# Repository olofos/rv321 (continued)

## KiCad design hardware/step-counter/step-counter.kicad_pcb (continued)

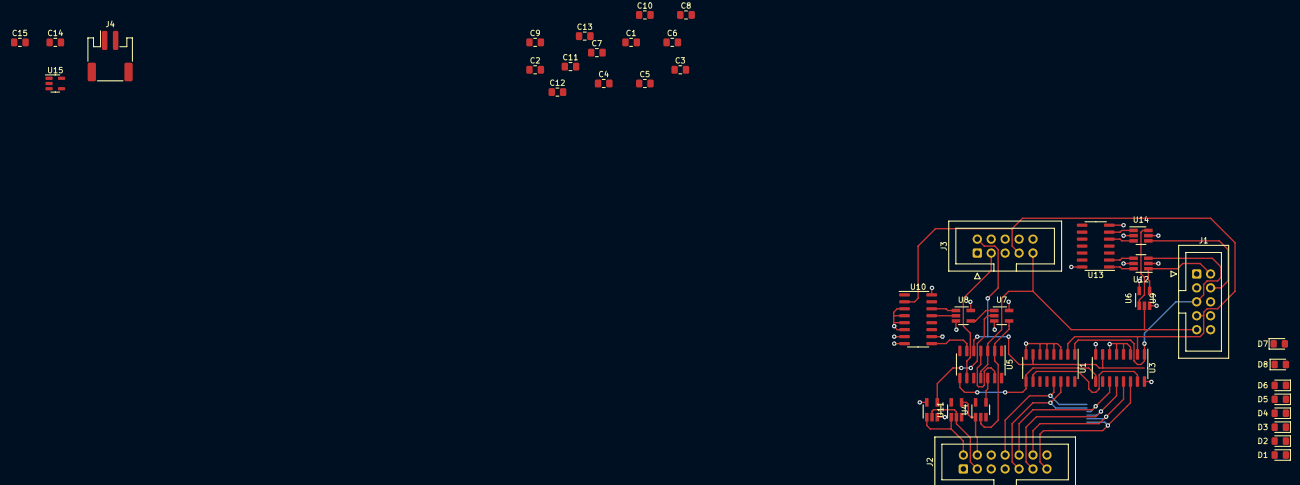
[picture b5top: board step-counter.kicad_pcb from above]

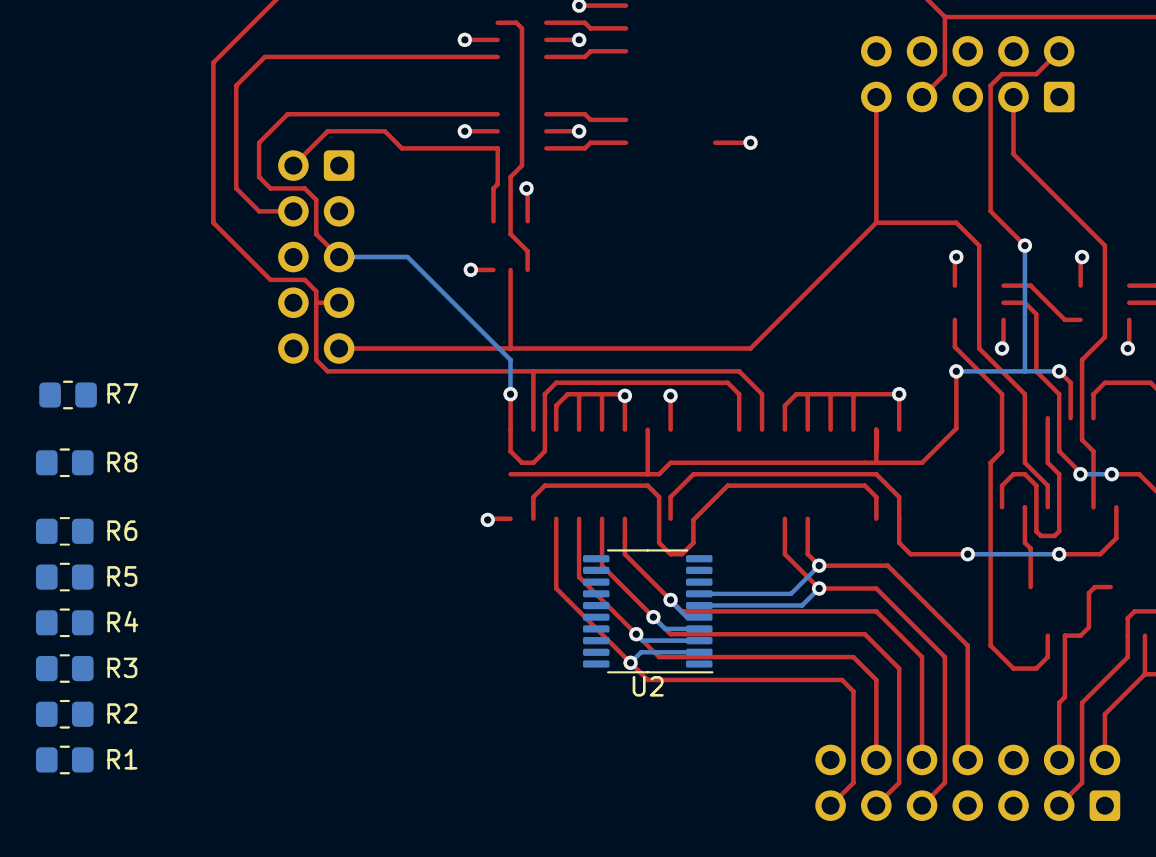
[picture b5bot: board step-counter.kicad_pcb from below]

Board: 4 copper layers, 50 parts (9 on the bottom side), 49 nets.

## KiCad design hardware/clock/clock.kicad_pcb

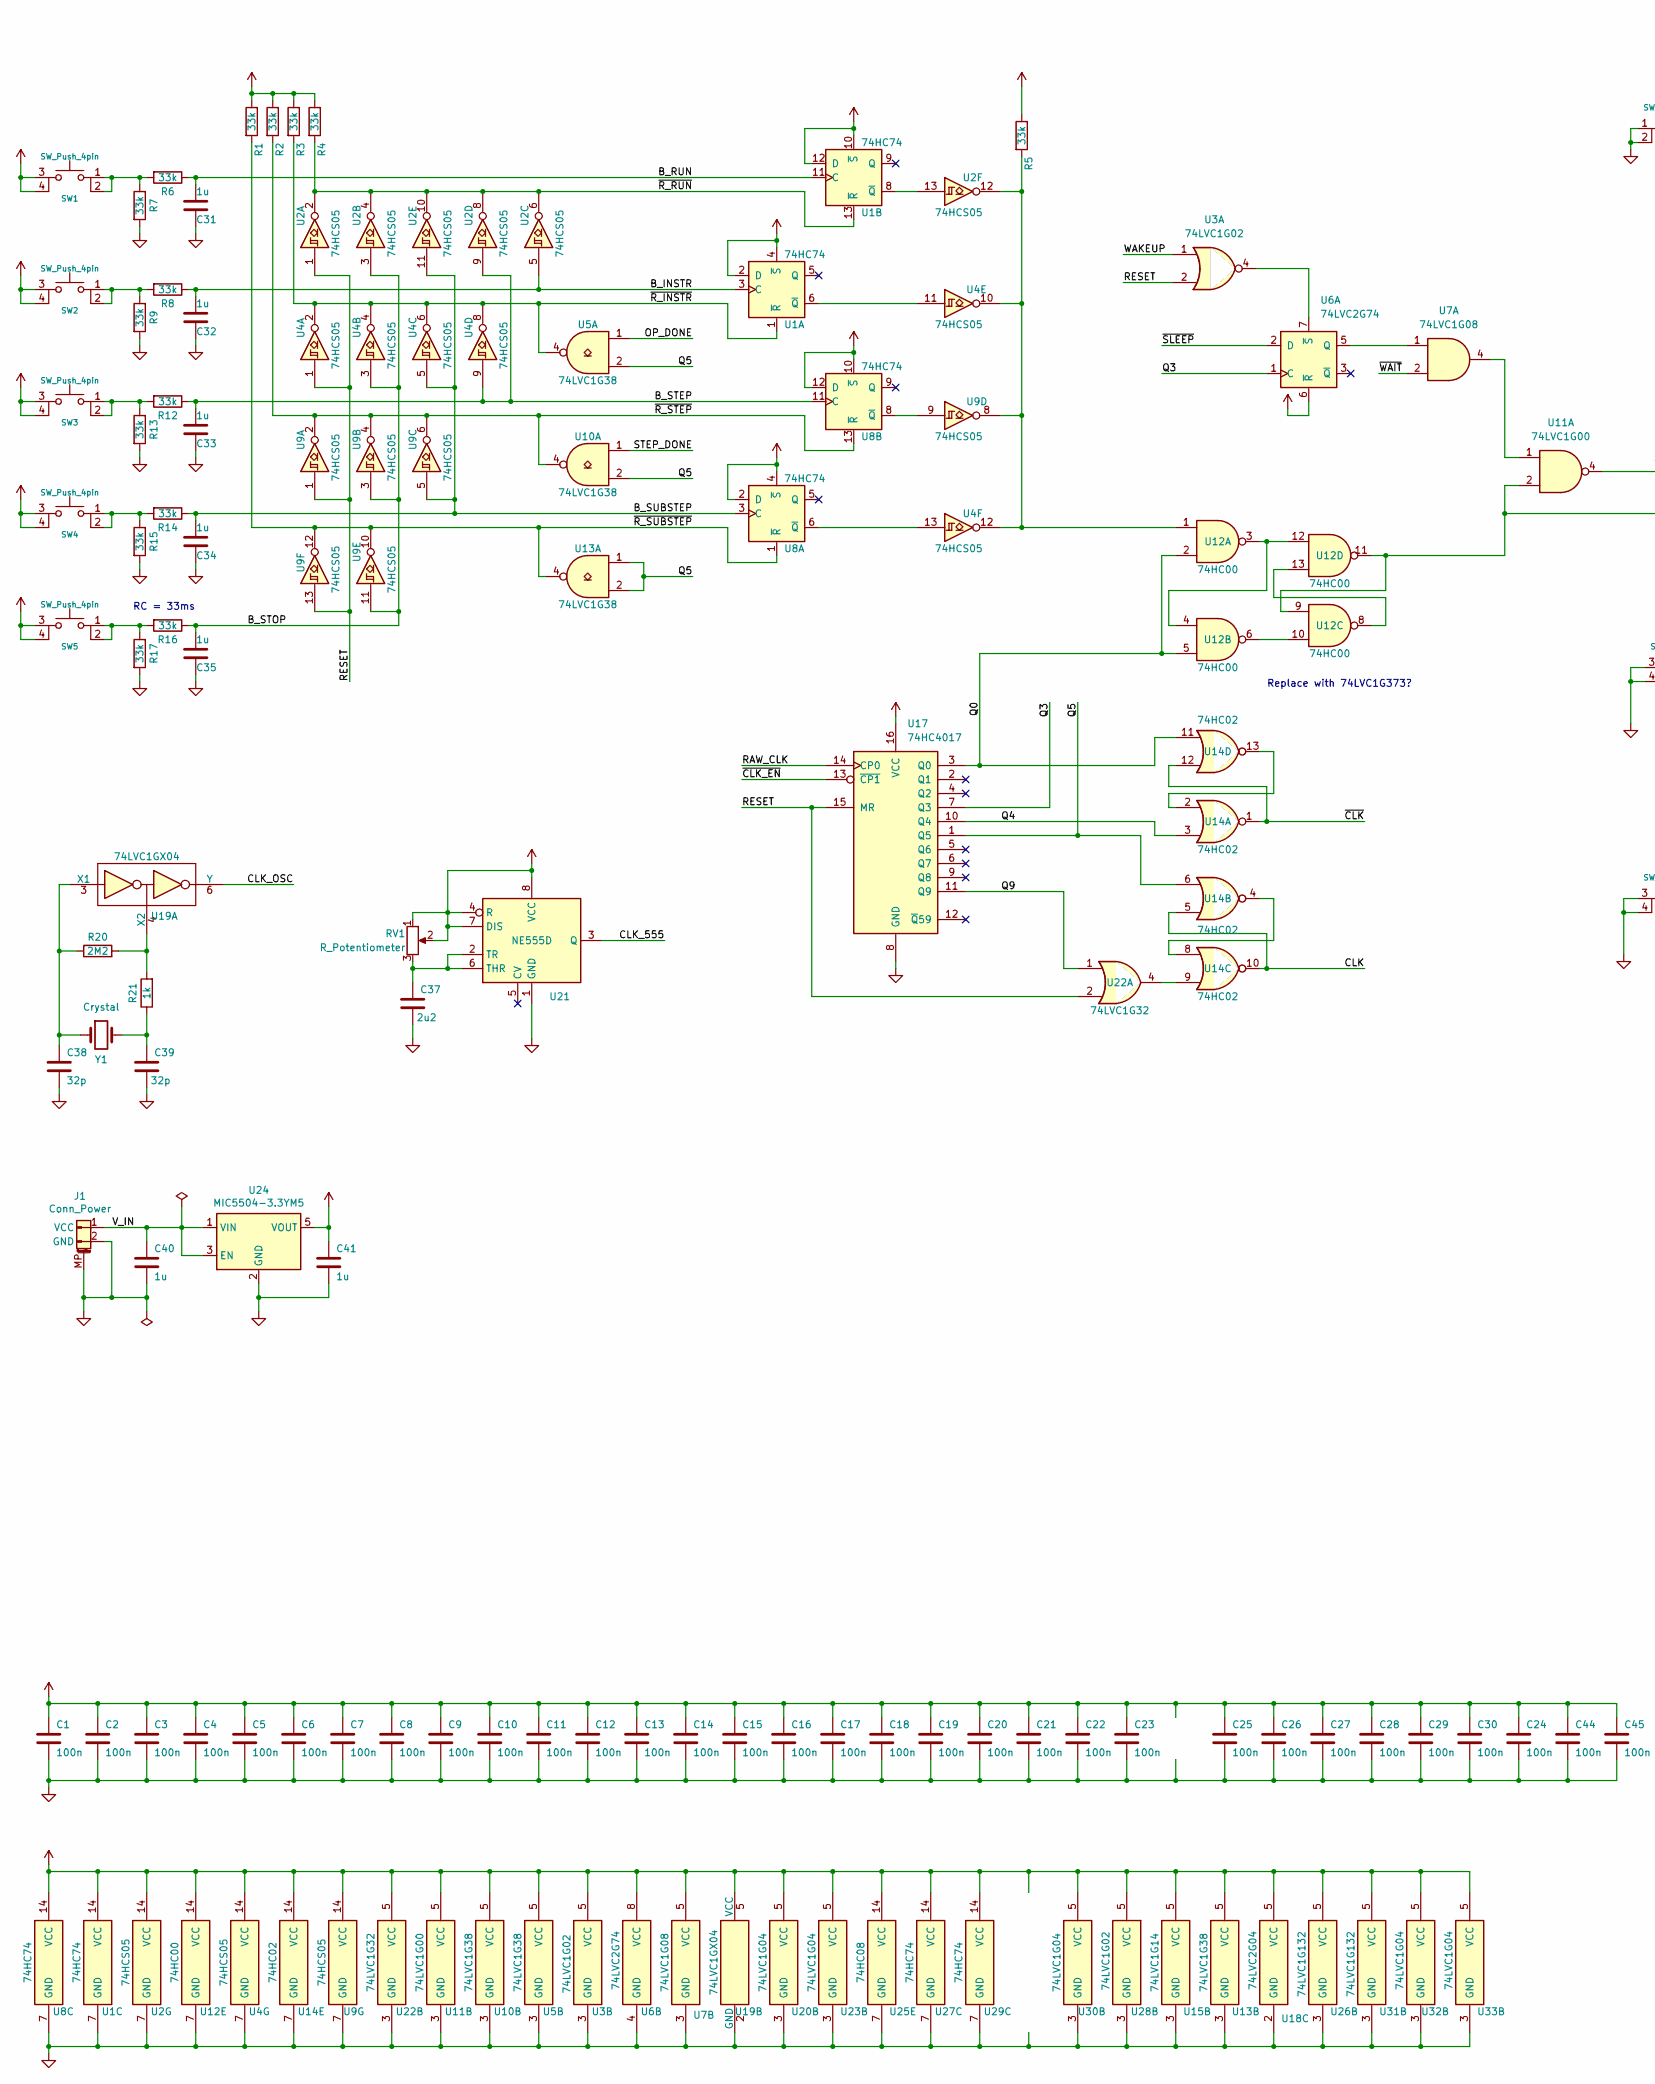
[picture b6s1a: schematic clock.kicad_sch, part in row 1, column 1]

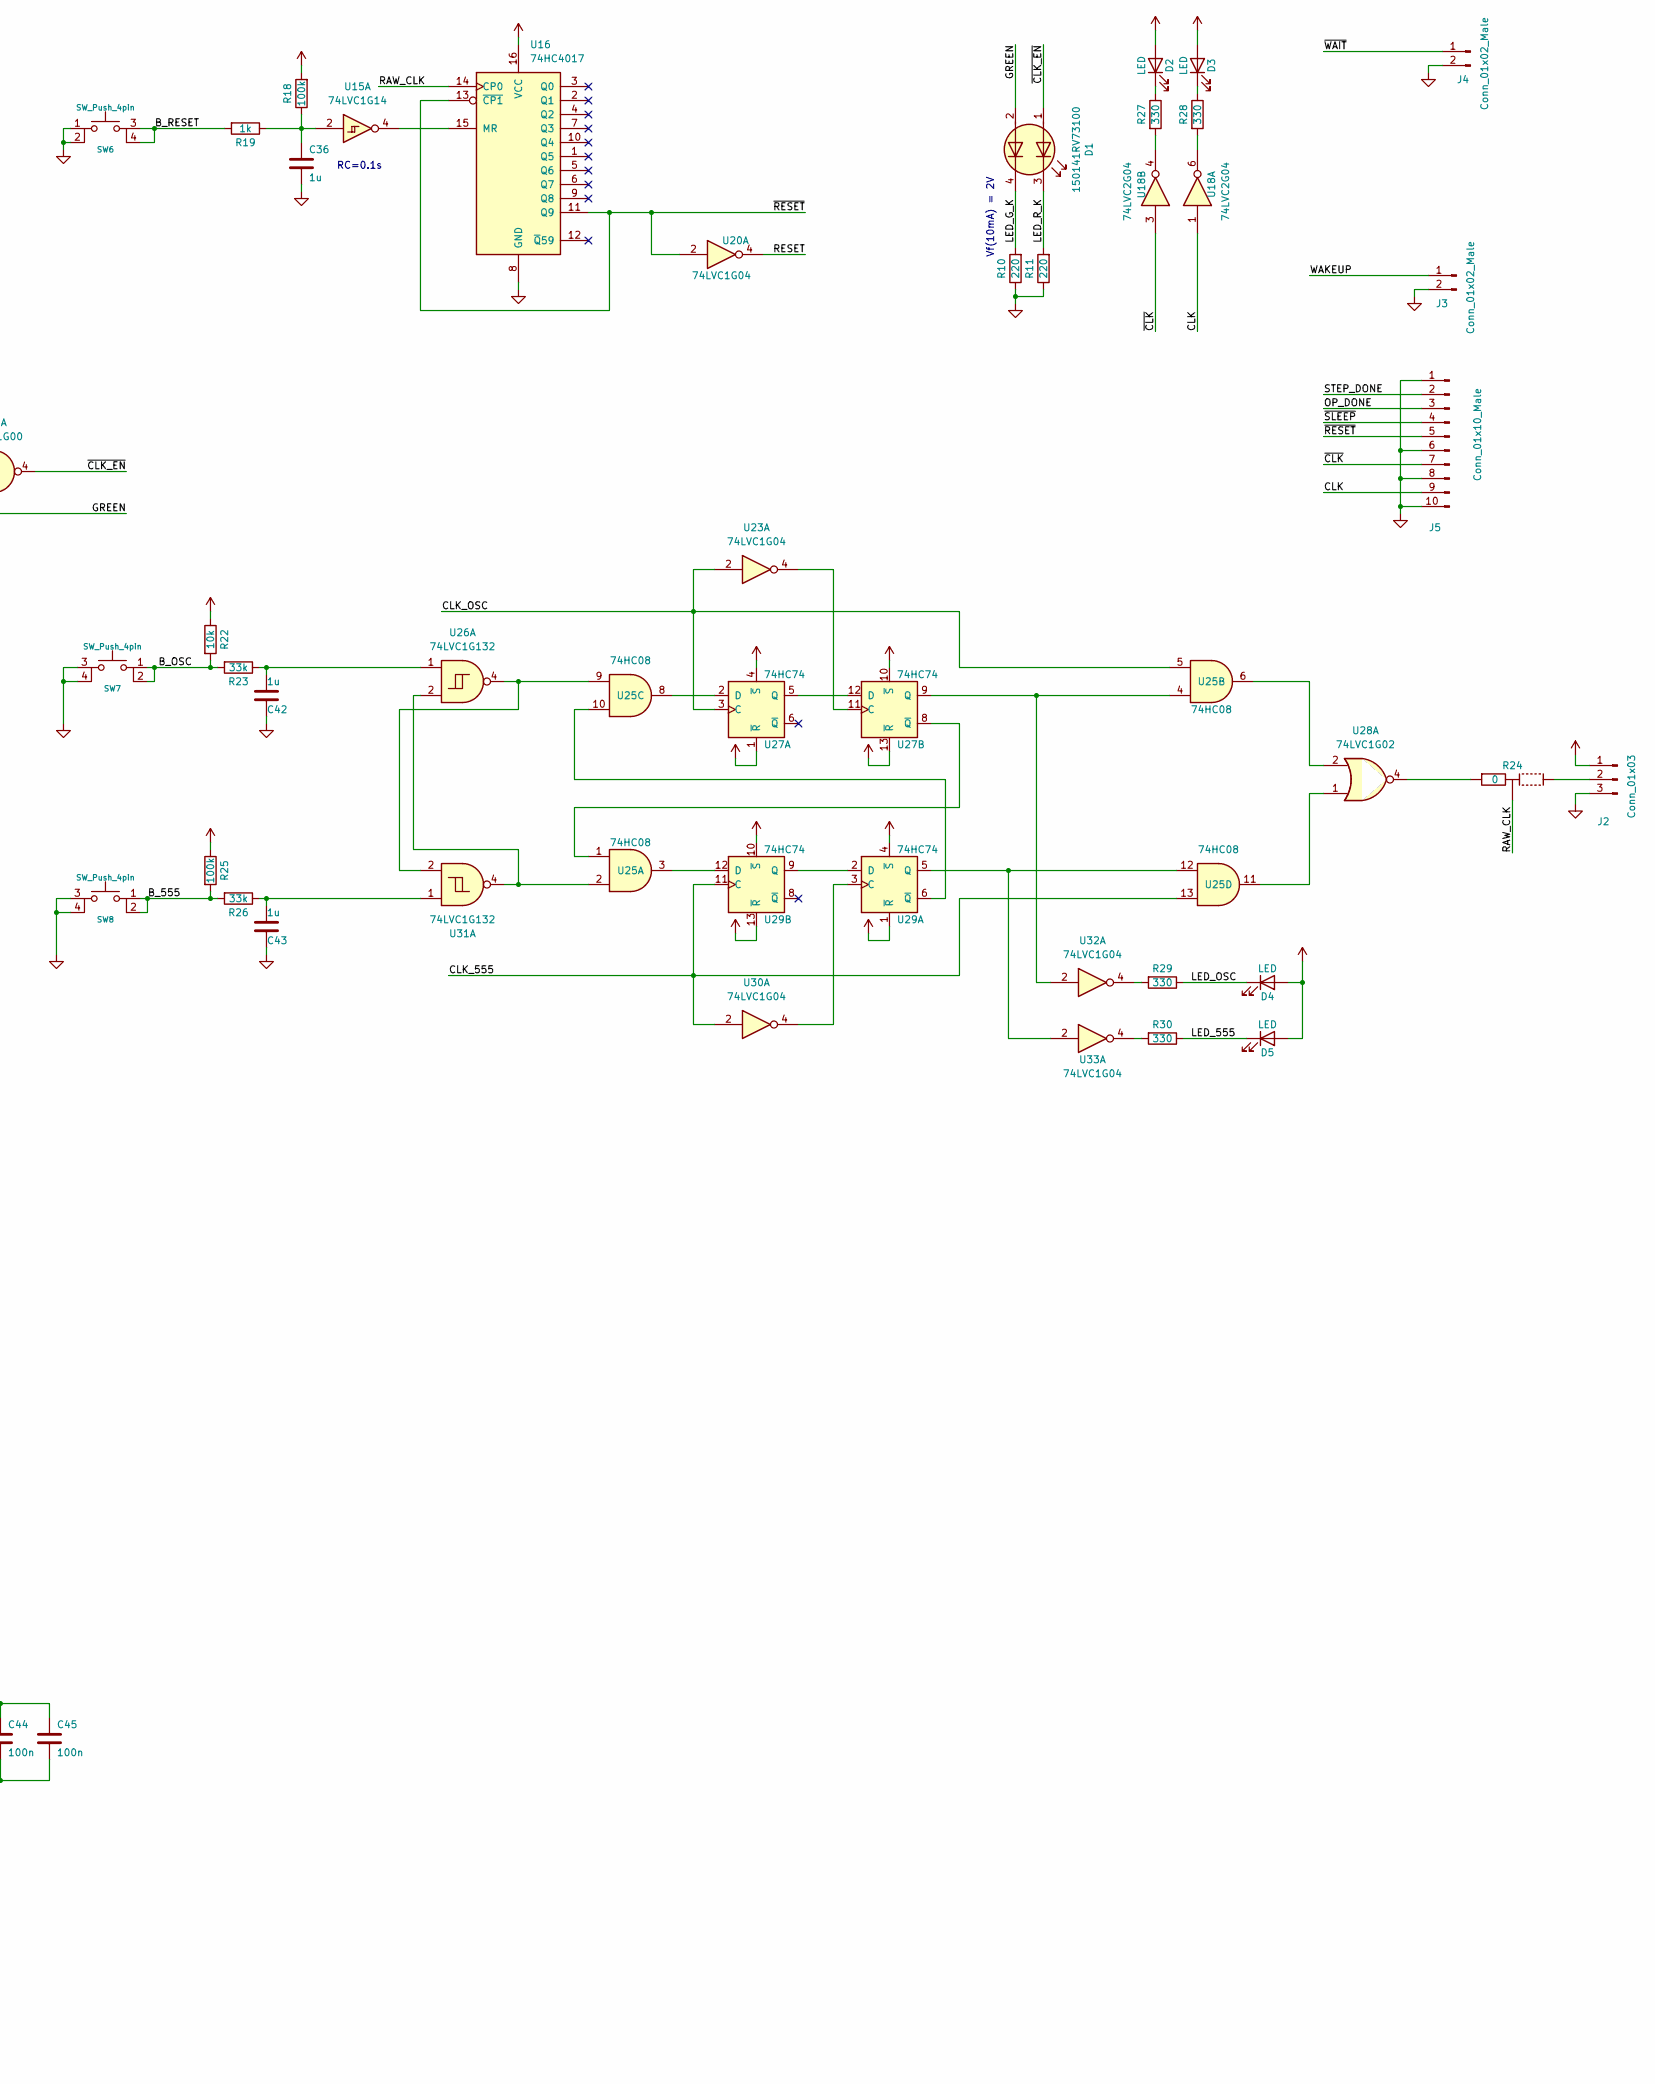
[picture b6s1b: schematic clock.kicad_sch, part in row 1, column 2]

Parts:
C1, C2, C3, C4, C5, C6, C7, C8, C9, C10, C11, C12, C13, C14, C15, C16, C17, C18, C19, C20, C21, C22, C23, C24, C25, C26, C27, C28, C29, C30, C44, C45: 100n; C_0805_2012Metric_Pad1.18x1.45mm_HandSolder
C31, C32, C33, C34, C35, C36, C40, C41, C42, C43: 1u; C_0805_2012Metric_Pad1.18x1.45mm_HandSolder
C37: 2u2; C_0805_2012Metric_Pad1.18x1.45mm_HandSolder
C38, C39: 32p; C_0805_2012Metric_Pad1.18x1.45mm_HandSolder
D1: 150141RV73100; Wurth WL-SBTW
D2, D3, D4, D5: LED; LED_0805_2012Metric_Pad1.15x1.40mm_HandSolder
J1: Conn_Power; JST_PH_S2B-PH-SM4-TB_1x02-1MP_P2.00mm_Horizontal
J2: Conn_01x03; PinHeader_1x03_P2.54mm_Vertical
J3, J4: Conn_01x02_Male; PinHeader_1x02_P2.54mm_Vertical
J5: Conn_01x10_Male; IDC-Header_2x05_P2.54mm_Vertical
R1, R2, R3, R4, R5, R6, R7, R8, R9, R12, R13, R14, R15, R16, R17, R23, R26: 33k; R_0805_2012Metric_Pad1.20x1.40mm_HandSolder
R10, R11: 220; R_0805_2012Metric_Pad1.20x1.40mm_HandSolder
R18, R25: 100k; R_0805_2012Metric_Pad1.20x1.40mm_HandSolder
R19, R21: 1k; R_0805_2012Metric_Pad1.20x1.40mm_HandSolder
R20: 2M2; R_0805_2012Metric_Pad1.20x1.40mm_HandSolder
R22: 10k; R_0805_2012Metric_Pad1.20x1.40mm_HandSolder
R24: 0; Jumper_3_R_0805
R27, R28, R29, R30: 330; R_0805_2012Metric_Pad1.20x1.40mm_HandSolder
RV1: R_Potentiometer; Potentiometer_Bourns_PTV09A-1_Single_Vertical
SW1, SW2, SW3, SW4, SW5, SW6, SW7, SW8: SW_Push_4pin; SW_SPST_DTSM-6
U1, U8, U27, U29: 74HC74; SOIC-14_3.9x8.7mm_P1.27mm
U2, U4, U9: 74HCS05; SOIC-14_3.9x8.7mm_P1.27mm
U3, U28: 74LVC1G02; SOT-23-5_HandSoldering
U5, U10, U13: 74LVC1G38; SOT-23-5_HandSoldering
U6: 74LVC2G74; TSSOP-8_3x3mm_P0.65mm
U7: 74LVC1G08; SOT-23-5_HandSoldering
U11: 74LVC1G00; SOT-23-5_HandSoldering
U12: 74HC00; SOIC-14_3.9x8.7mm_P1.27mm
U14: 74HC02; SOIC-14_3.9x8.7mm_P1.27mm
U15: 74LVC1G14; SOT-23-5_HandSoldering
U16, U17: 74HC4017; SOIC-16_3.9x9.9mm_P1.27mm
U18: 74LVC2G04; SOT-23-6_Handsoldering
U19: 74LVC1GX04; SOT-23-6_Handsoldering
U20, U23, U30, U32, U33: 74LVC1G04; SOT-23-5_HandSoldering
U21: NE555D; SOIC-8_3.9x4.9mm_P1.27mm
U22: 74LVC1G32; SOT-23-5_HandSoldering
U24: MIC5504-3.3YM5; SOT-23-5
U25: 74HC08; SOIC-14_3.9x8.7mm_P1.27mm
U26, U31: 74LVC1G132; SOT-23-5_HandSoldering
Y1: Crystal; Crystal_HC49-U_Vertical

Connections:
/B_555: R25.2, R26.2, SW8.1, SW8.2
/B_INSTR: C32.1, R8.1, U1.3 (C), U2.5
/B_OSC: R22.2, R23.2, SW7.1, SW7.2
/B_RESET: R19.2, SW6.3, SW6.4
/B_RUN: C31.1, R6.1, U1.11 (C)
/B_STEP: C33.1, R12.1, U2.9, U4.9, U8.11 (C)
/B_STOP: C35.1, R16.1, U2.3, U4.3, U9.3, U9.11
/B_SUBSTEP: C34.1, R14.1, U2.11, U4.5, U8.3 (C), U9.5
/CLK: J5.9, U14.5, U14.10, U18.1
/CLK_555: U21.3 (Q), U25.13, U29.11 (C), U30.2
/CLK_OSC: U19.6 (Y), U23.2, U25.5, U27.3 (C)
/GREEN: D1.2 (A2), U11.2, U12.9, U12.11
/LED_555: D5.1 (K), R30.1
/LED_G_K: D1.4 (K2), R10.2
/LED_OSC: D4.1 (K), R29.1
/LED_R_K: D1.3 (K1), R11.2
/OP_DONE: J5.3, U5.1
/Q0: U12.2, U12.5, U14.11, U17.3 (Q0)
/Q3: U6.1 (C), U17.7 (Q3)
/Q4: U14.3, U17.10 (Q4)
/Q5: U5.2, U10.2, U13.1, U13.2, U14.6, U17.1 (Q5)
/Q9: U17.11 (Q9), U22.1
/RAW_CLK: R24.2, U16.14 (CP0), U17.14 (CP0)
/RESET: U2.1, U3.2, U4.1, U9.1, U9.13, U17.15 (MR), U20.4, U22.2
/STEP_DONE: J5.2, U10.1
/V_IN: C40.1, J1.1 (VCC), U24.1 (VIN), U24.3 (EN)
/WAKEUP: J3.1, U3.1
/~CLK_EN: D1.1 (A1), U11.4, U17.13 (~CP1)
/~CLK: J5.7, U14.1, U14.12, U18.3
/~RESET: J5.5, U16.11 (Q9), U16.13 (~CP1), U20.2
/~R_INSTR: R3.2, U1.1 (~R), U4.2, U4.4, U4.6, U4.8, U5.4
/~R_RUN: R4.2, U1.13 (~R), U2.2, U2.4, U2.6, U2.8, U2.10
/~R_STEP: R2.2, U8.13 (~R), U9.2, U9.4, U9.6, U10.4
/~R_SUBSTEP: R1.2, U8.1 (~R), U9.10, U9.12, U13.4
/~SLEEP: J5.4, U6.2 (D)
/~WAIT: J4.1, U7.2
GND: C1.2, C2.2, C3.2, C4.2, C5.2, C6.2, C7.2, C8.2, C9.2, C10.2, C11.2, C12.2, C13.2, C14.2, C15.2, C16.2, C17.2, C18.2, C19.2, C20.2, C21.2, C22.2, C23.2, C24.2, C25.2, C26.2, C27.2, C28.2, C29.2, C30.2, C31.2, C32.2, C33.2, C34.2, C35.2, C36.2, C37.2, C38.2, C39.2, C40.2, C41.2, C42.2, C43.2, C44.2, C45.2, J1.2 (GND), J1.MP, J2.3, J3.2, J4.2, J5.1, J5.6, J5.8, J5.10, R7.2, R9.2, R10.1, R11.1, R13.2, R15.2, R17.2, SW6.1, SW6.2, SW7.3, SW7.4, SW8.3, SW8.4, U1.7 (GND), U2.7 (GND), U3.3 (GND), U4.7 (GND), U5.3 (GND), U6.4 (GND), U7.3 (GND), U8.7 (GND), U9.7 (GND), U10.3 (GND), U11.3 (GND), U12.7 (GND), U13.3 (GND), U14.7 (GND), U15.3 (GND), U16.8 (GND), U17.8 (GND), U18.2 (GND), U19.2 (GND), U20.3 (GND), U21.1 (GND), U22.3 (GND), U23.3 (GND), U24.2 (GND), U25.7 (GND), U26.3 (GND), U27.7 (GND), U28.3 (GND), U29.7 (GND), U30.3 (GND), U31.3 (GND), U32.3 (GND), U33.3 (GND)
unnamed: C36.1, R18.1, R19.1, U15.2
unnamed: C37.1, RV1.3, U21.2 (TR), U21.6 (THR)
unnamed: C38.1, R20.1, U19.3 (X1), Y1.1
unnamed: C39.1, R21.1, Y1.2
unnamed: C42.1, R23.1, U26.1
unnamed: C43.1, R26.1, U31.1
unnamed: D2.1 (K), R27.1
unnamed: D3.1 (K), R28.1
unnamed: J2.2, R24.3
unnamed: R5.2, U2.12, U4.10, U4.12, U9.8, U12.1
unnamed: R6.2, R7.1, SW1.1, SW1.2
unnamed: R8.2, R9.1, SW2.1, SW2.2
unnamed: R12.2, R13.1, SW3.1, SW3.2
unnamed: R14.2, R15.1, SW4.1, SW4.2
unnamed: R16.2, R17.1, SW5.1, SW5.2
unnamed: R20.2, R21.2, U19.4 (X2)
unnamed: R24.1, U28.4
unnamed: R27.2, U18.4
unnamed: R28.2, U18.6
unnamed: R29.2, U32.4
unnamed: R30.2, U33.4
unnamed: U1.6 (~Q), U4.11
unnamed: U1.8 (~Q), U2.13
unnamed: U3.4, U6.7 (~S)
unnamed: U4.13, U8.6 (~Q)
unnamed: U6.5 (Q), U7.1
unnamed: U8.8 (~Q), U9.9
unnamed: U7.4, U11.1
unnamed: U12.6, U12.10
unnamed: U12.3, U12.4, U12.12
unnamed: U12.8, U12.13
unnamed: U14.4, U14.8
unnamed: U14.9, U22.4
unnamed: U14.2, U14.13
unnamed: U15.4, U16.15 (MR)
unnamed: U23.4, U27.11 (C)
unnamed: U25.1, U27.8 (~Q)
unnamed: U25.2, U26.2, U31.4
unnamed: U25.3, U29.12 (D)
unnamed: U25.4, U27.9 (Q), U32.2
unnamed: U25.6, U28.2
unnamed: U25.8, U27.2 (D)
unnamed: U25.9, U26.4, U31.2
unnamed: U25.10, U29.6 (~Q)
unnamed: U25.11, U28.1
unnamed: U25.12, U29.5 (Q), U33.2
unnamed: U27.5 (Q), U27.12 (D)
unnamed: U29.2 (D), U29.9 (Q)
unnamed: U29.3 (C), U30.4
VCC: C1.1, C2.1, C3.1, C4.1, C5.1, C6.1, C7.1, C8.1, C9.1, C10.1, C11.1, C12.1, C13.1, C14.1, C15.1, C16.1, C17.1, C18.1, C19.1, C20.1, C21.1, C22.1, C23.1, C24.1, C25.1, C26.1, C27.1, C28.1, C29.1, C30.1, C41.1, C44.1, C45.1, D2.2 (A), D3.2 (A), D4.2 (A), D5.2 (A), J2.1, R1.1, R2.1, R3.1, R4.1, R5.1, R18.2, R22.1, R25.1, RV1.1, RV1.2, SW1.3, SW1.4, SW2.3, SW2.4, SW3.3, SW3.4, SW4.3, SW4.4, SW5.3, SW5.4, U1.2 (D), U1.4 (~S), U1.10 (~S), U1.12 (D), U1.14 (VCC), U2.14 (VCC), U3.5 (VCC), U4.14 (VCC), U5.5 (VCC), U6.6 (~R), U6.8 (VCC), U7.5 (VCC), U8.2 (D), U8.4 (~S), U8.10 (~S), U8.12 (D), U8.14 (VCC), U9.14 (VCC), U10.5 (VCC), U11.5 (VCC), U12.14 (VCC), U13.5 (VCC), U14.14 (VCC), U15.5 (VCC), U16.16 (VCC), U17.16 (VCC), U18.5 (VCC), U19.5 (VCC), U20.5 (VCC), U21.4 (R), U21.7 (DIS), U21.8 (VCC), U22.5 (VCC), U23.5 (VCC), U24.5 (VOUT), U25.14 (VCC), U26.5 (VCC), U27.1 (~R), U27.4 (~S), U27.10 (~S), U27.13 (~R), U27.14 (VCC), U28.5 (VCC), U29.1 (~R), U29.4 (~S), U29.10 (~S), U29.13 (~R), U29.14 (VCC), U30.5 (VCC), U31.5 (VCC), U32.5 (VCC), U33.5 (VCC)

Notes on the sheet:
Vf(10mA) = 2V
RC=0.1s
RC = 33ms
Replace with 74LVC1G373?

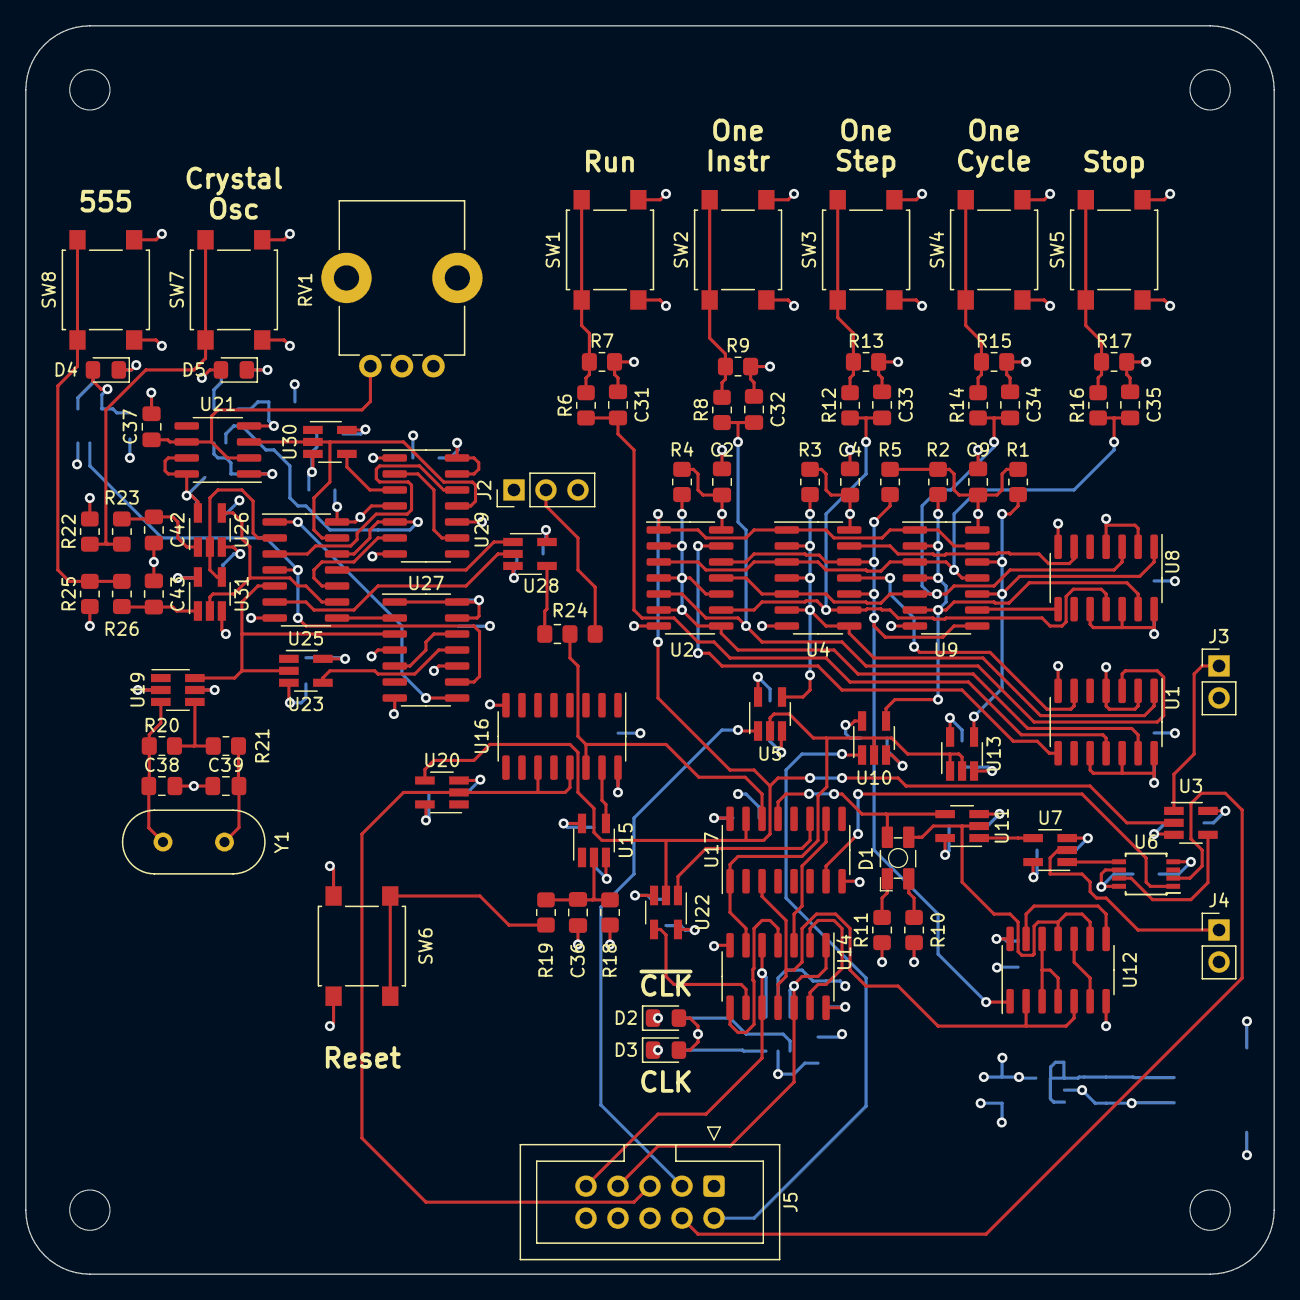
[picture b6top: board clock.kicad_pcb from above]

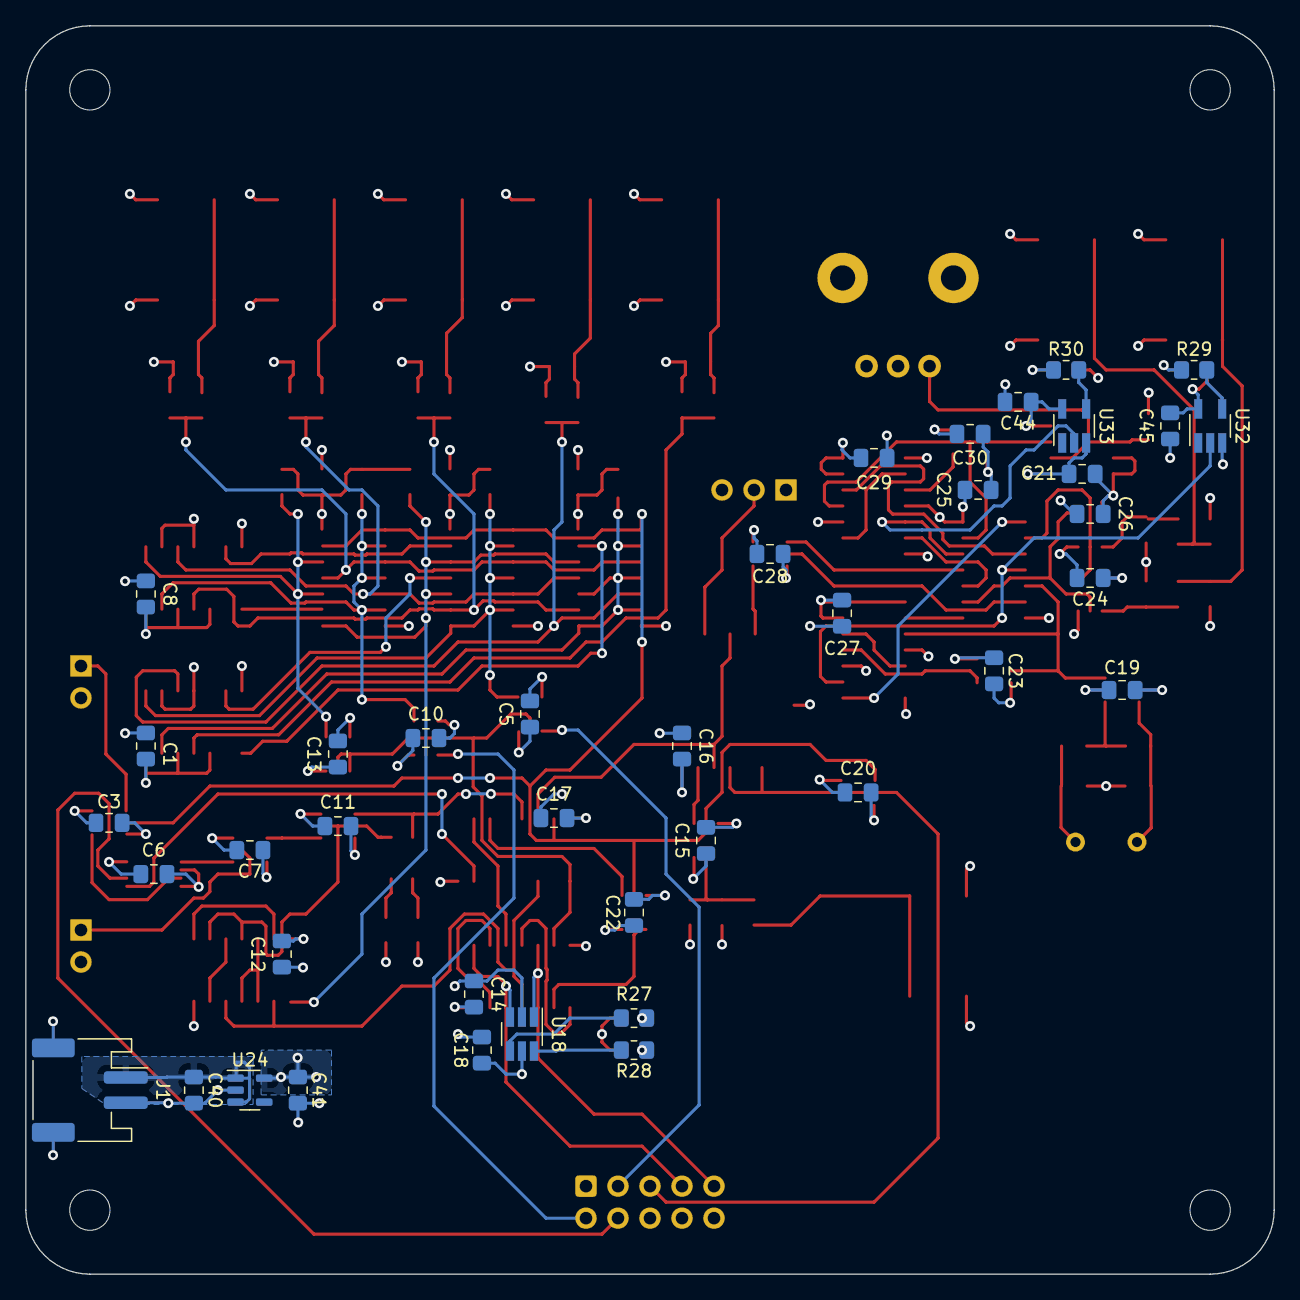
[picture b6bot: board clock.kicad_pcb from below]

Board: 4 copper layers, 99.1 x 99.1 mm, 128 parts (40 on the bottom side), 87 nets.

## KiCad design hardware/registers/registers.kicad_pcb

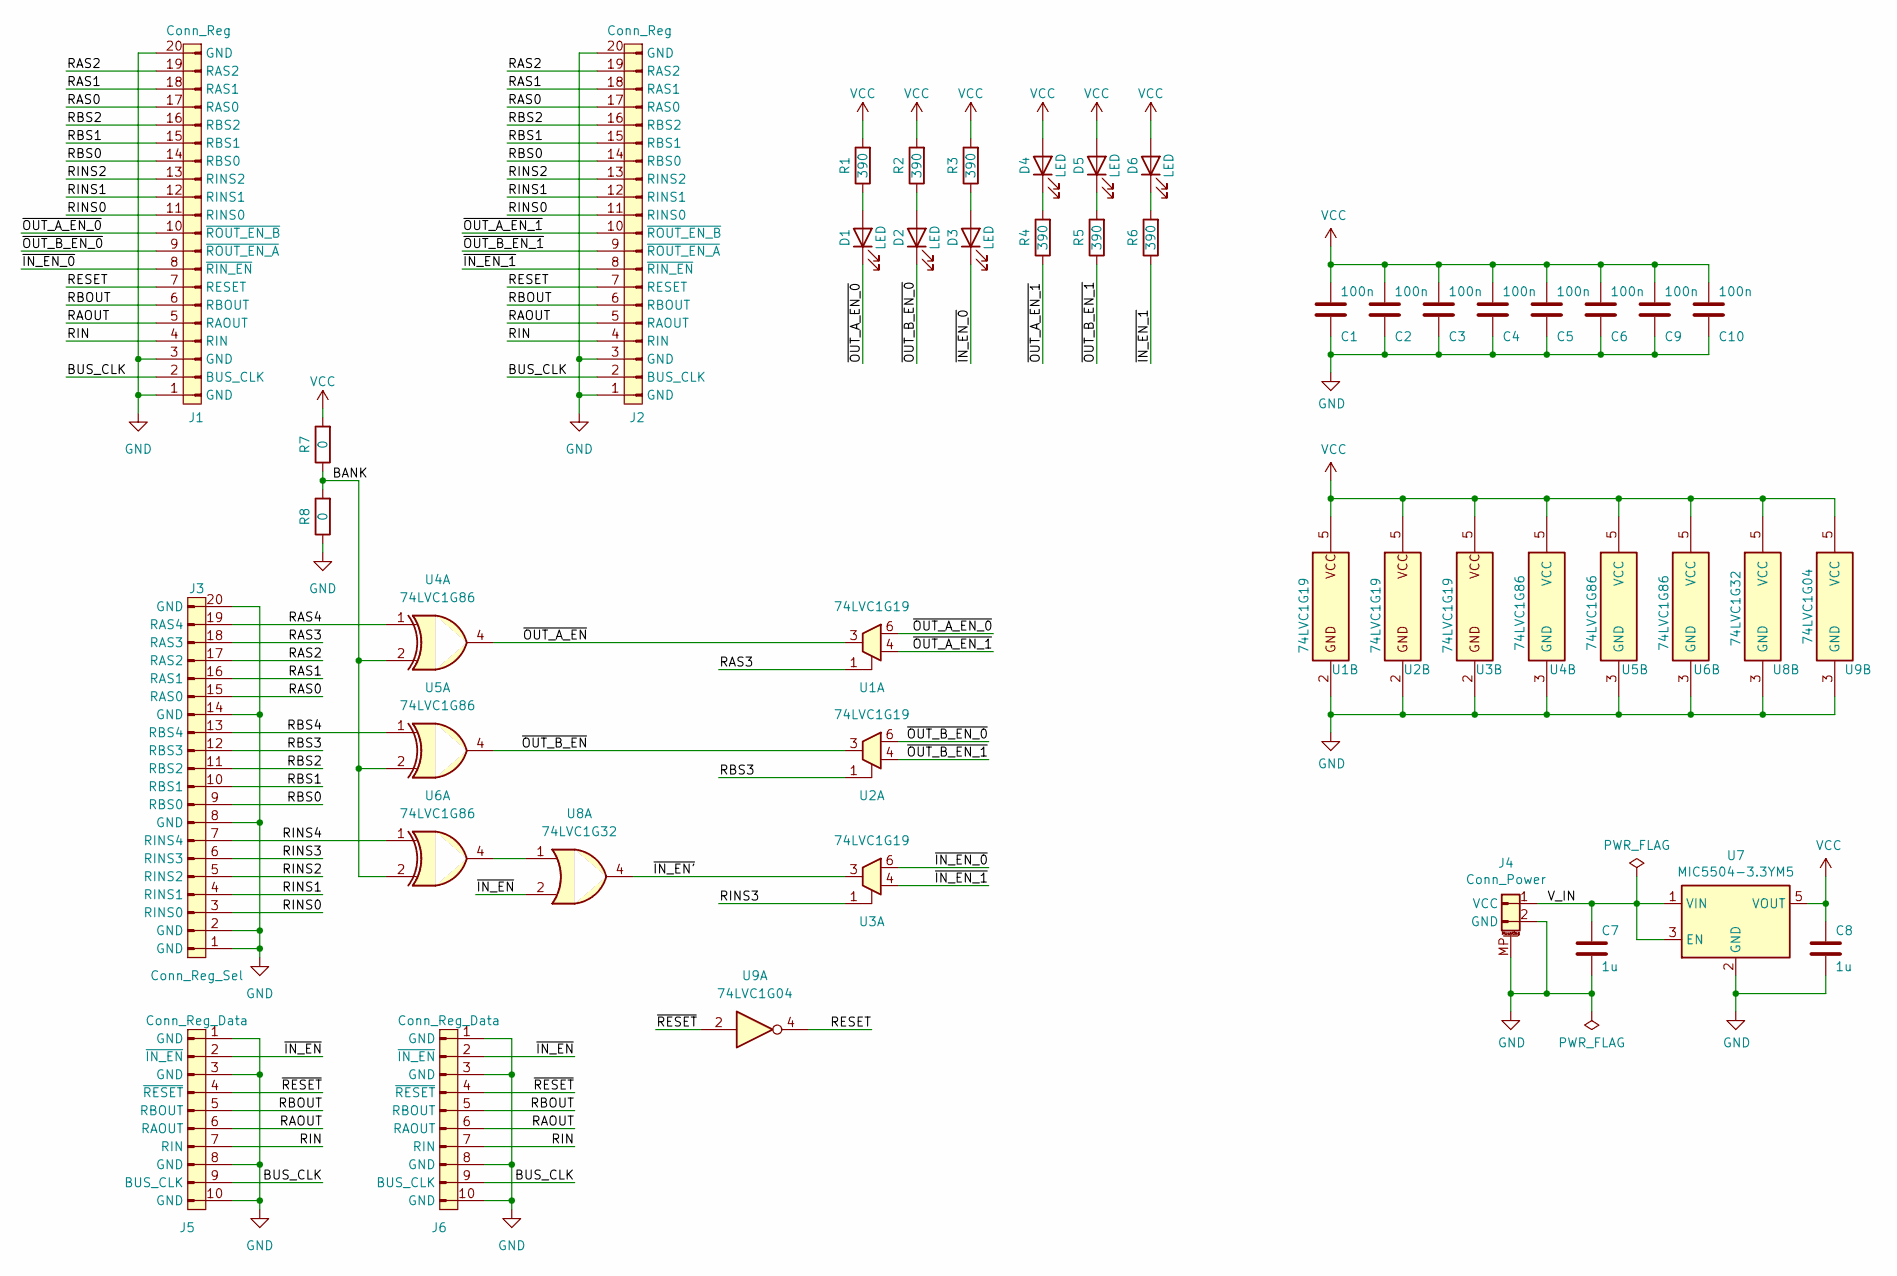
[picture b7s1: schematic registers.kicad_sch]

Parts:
C1, C2, C3, C4, C5, C6, C9, C10: 100n; C_0805_2012Metric_Pad1.18x1.45mm_HandSolder
C7, C8: 1u; C_0805_2012Metric_Pad1.18x1.45mm_HandSolder
D1, D2, D3, D4, D5, D6: LED; LED_0805_2012Metric_Pad1.15x1.40mm_HandSolder
J1, J2: Conn_Reg; IDC-Header_2x10_P2.54mm_Vertical
J3: Conn_Reg_Sel; IDC-Header_2x10_P2.54mm_Vertical
J4: Conn_Power; JST_PH_S2B-PH-SM4-TB_1x02-1MP_P2.00mm_Horizontal
J5, J6: Conn_Reg_Data; IDC-Header_2x05_P2.54mm_Vertical
R1, R2, R3, R4, R5, R6: 390; R_0805_2012Metric_Pad1.20x1.40mm_HandSolder
R7, R8: 0; R_0805_2012Metric_Pad1.20x1.40mm_HandSolder
U1, U2, U3: 74LVC1G19; SOT-23-6_Handsoldering
U4, U5, U6: 74LVC1G86; SOT-23-5_HandSoldering
U7: MIC5504-3.3YM5; SOT-23-5_HandSoldering
U8: 74LVC1G32; SOT-23-5_HandSoldering
U9: 74LVC1G04; SOT-23-5_HandSoldering

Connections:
/BANK: R7.1, R8.2, U4.2, U5.2, U6.2
/BUS_CLK: J1.2 (BUS_CLK), J2.2 (BUS_CLK), J5.9 (BUS_CLK), J6.9 (BUS_CLK)
/RAOUT: J1.5 (RAOUT), J2.5 (RAOUT), J5.6 (RAOUT), J6.6 (RAOUT)
/RAS0: J1.17 (RAS0), J2.17 (RAS0), J3.15 (RAS0)
/RAS1: J1.18 (RAS1), J2.18 (RAS1), J3.16 (RAS1)
/RAS2: J1.19 (RAS2), J2.19 (RAS2), J3.17 (RAS2)
/RAS3: J3.18 (RAS3), U1.1 (S)
/RAS4: J3.19 (RAS4), U4.1
/RBOUT: J1.6 (RBOUT), J2.6 (RBOUT), J5.5 (RBOUT), J6.5 (RBOUT)
/RBS0: J1.14 (RBS0), J2.14 (RBS0), J3.9 (RBS0)
/RBS1: J1.15 (RBS1), J2.15 (RBS1), J3.10 (RBS1)
/RBS2: J1.16 (RBS2), J2.16 (RBS2), J3.11 (RBS2)
/RBS3: J3.12 (RBS3), U2.1 (S)
/RBS4: J3.13 (RBS4), U5.1
/RESET: J1.7 (RESET), J2.7 (RESET), U9.4
/RIN: J1.4 (RIN), J2.4 (RIN), J5.7 (RIN), J6.7 (RIN)
/RINS0: J1.11 (RINS0), J2.11 (RINS0), J3.3 (RINS0)
/RINS1: J1.12 (RINS1), J2.12 (RINS1), J3.4 (RINS1)
/RINS2: J1.13 (RINS2), J2.13 (RINS2), J3.5 (RINS2)
/RINS3: J3.6 (RINS3), U3.1 (S)
/RINS4: J3.7 (RINS4), U6.1
/V_IN: C7.1, J4.1 (VCC), U7.1 (VIN), U7.3 (EN)
/~IN_EN': U3.3 (I), U8.4
/~IN_EN_0: D3.1 (K), J1.8 (~RIN_EN), U3.6 (Y0)
/~IN_EN_1: J2.8 (~RIN_EN), R6.1, U3.4 (Y1)
/~IN_EN: J5.2 (~IN_EN), J6.2 (~IN_EN), U8.2
/~OUT_A_EN_0: D1.1 (K), J1.10 (~ROUT_EN_B), U1.6 (Y0)
/~OUT_A_EN_1: J2.10 (~ROUT_EN_B), R4.1, U1.4 (Y1)
/~OUT_A_EN: U1.3 (I), U4.4
/~OUT_B_EN_0: D2.1 (K), J1.9 (~ROUT_EN_A), U2.6 (Y0)
/~OUT_B_EN_1: J2.9 (~ROUT_EN_A), R5.1, U2.4 (Y1)
/~OUT_B_EN: U2.3 (I), U5.4
/~RESET: J5.4 (~RESET), J6.4 (~RESET), U9.2
GND: C1.2, C2.2, C3.2, C4.2, C5.2, C6.2, C7.2, C8.2, C9.2, C10.2, J1.1 (GND), J1.3 (GND), J1.20 (GND), J2.1 (GND), J2.3 (GND), J2.20 (GND), J3.1 (GND), J3.2 (GND), J3.8 (GND), J3.14 (GND), J3.20 (GND), J4.2 (GND), J4.MP, J5.1 (GND), J5.3 (GND), J5.8 (GND), J5.10 (GND), J6.1 (GND), J6.3 (GND), J6.8 (GND), J6.10 (GND), R8.1, U1.2 (GND), U2.2 (GND), U3.2 (GND), U4.3 (GND), U5.3 (GND), U6.3 (GND), U7.2 (GND), U8.3 (GND), U9.3 (GND)
unnamed: D1.2 (A), R1.1
unnamed: D2.2 (A), R2.1
unnamed: D3.2 (A), R3.1
unnamed: D4.1 (K), R4.2
unnamed: D5.1 (K), R5.2
unnamed: D6.1 (K), R6.2
unnamed: U6.4, U8.1
VCC: C1.1, C2.1, C3.1, C4.1, C5.1, C6.1, C8.1, C9.1, C10.1, D4.2 (A), D5.2 (A), D6.2 (A), R1.2, R2.2, R3.2, R7.2, U1.5 (VCC), U2.5 (VCC), U3.5 (VCC), U4.5 (VCC), U5.5 (VCC), U6.5 (VCC), U7.5 (VOUT), U8.5 (VCC), U9.5 (VCC)

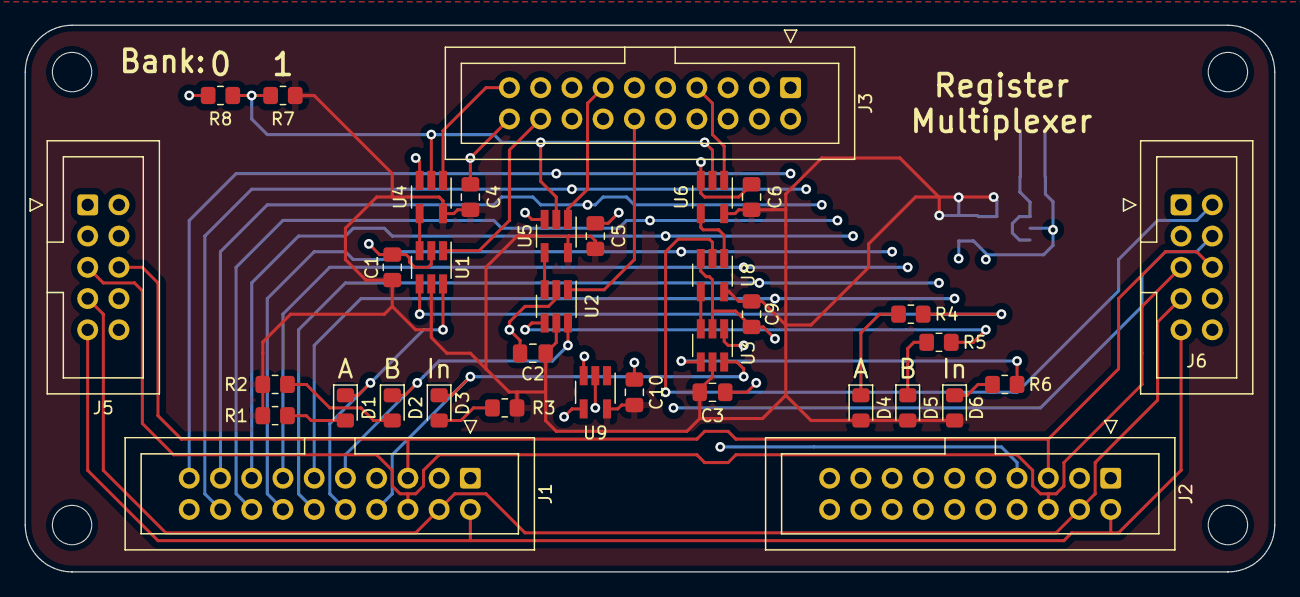
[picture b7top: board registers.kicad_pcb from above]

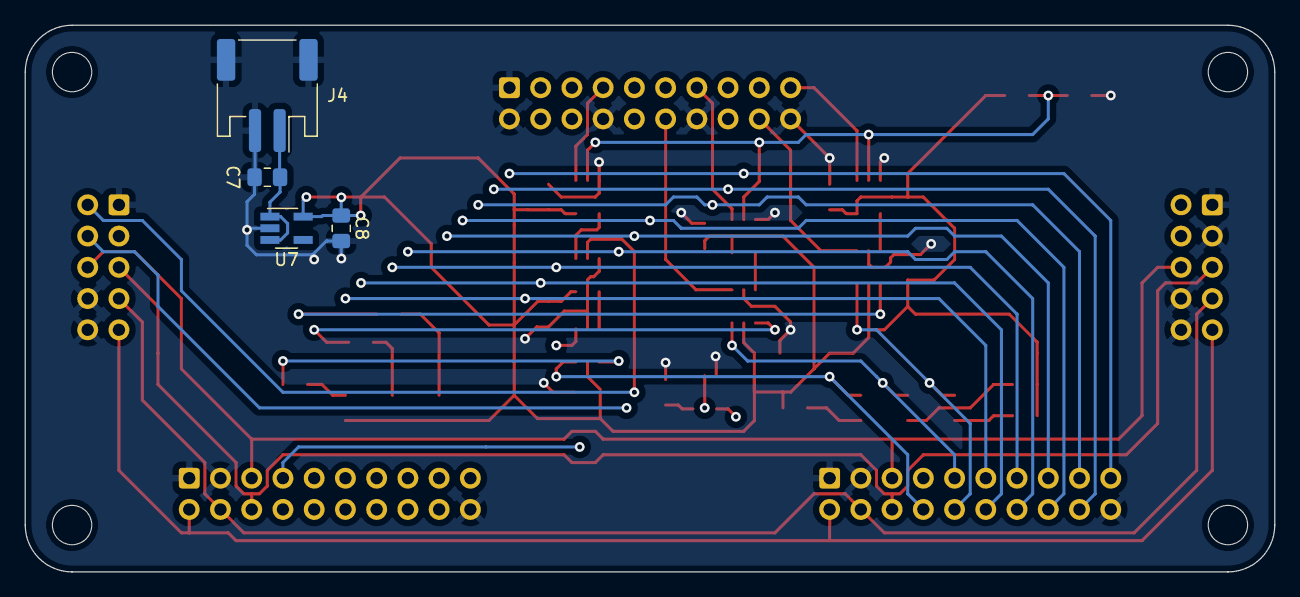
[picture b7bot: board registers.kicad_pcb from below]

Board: 4 copper layers, 101.6 x 44.4 mm, 39 parts (4 on the bottom side), 42 nets.
